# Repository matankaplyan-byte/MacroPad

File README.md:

# MacroPad

A fully customizable 6-key macro pad powered by a custom RP2040 PCB, featuring a rotary encoder, a 1.3-inch display, and a Python desktop application.

## The Idea

The goal is to create a macro pad with **unlimited custom layouts**.

Each layout contains six customizable macros. By pressing the rotary encoder's built-in button, users will be able to switch between layouts without opening the desktop application.

For example:

- **Layout 1 — Everyday:** WhatsApp, YouTube, Discord mute, media controls, etc.
- **Layout 2 — Programming:** Copy, paste, run code, open applications, and shortcuts.
- **Layout 3 — Sim Racing:** Game shortcuts and other racing-related controls.

Users will be able to create as many layouts as they want and customize the actions assigned to each key.

## Planned Hardware

- Custom RP2040-based PCB
- 6 mechanical keyboard switches
- EC11 rotary encoder with push button
- 1.3-inch ST7789 240×240 display
- USB-C connection
- Custom 3D-printed enclosure

The rotary encoder will control volume when rotated and switch between macro layouts when pressed.

The display is intended to show useful information about the currently selected layout and macros.

### PCB Design

I designed the custom PCB in KiCad, including the RP2040 microcontroller, USB-C connection, mechanical switches, rotary encoder, and display connector.

**Circuit schematic:**

**PCB layout:**

**PCB 3D preview:**

### 3D Modeling

I used Fusion 360 to design the enclosure and check how the components would fit together.

I imported models of the PCB components, including the switches, screen, and rotary encoder, to help position everything correctly.

**Component assembly in Fusion 360:**

The enclosure was designed as two separate pieces, with holes for heat-set inserts and screws to hold them together.

The first print still needs some improvements because the supports damaged the top part, but the bottom part printed successfully.

## Desktop Software

The controller is being developed in Python using Tkinter.

### Currently implemented

- Dark-themed desktop GUI
- Six selectable macro slots
- Arduino serial communication
- WhatsApp and YouTube launching
- Discord mute/unmute
- Media play/pause
- Custom macro editing
- Support for keyboard shortcuts, websites, and launching applications
- Creating and deleting custom layouts
- Saving layouts and macros using JSON
- Rotary encoder volume control in the Arduino prototype
- OLED display support in the Arduino prototype

### Planned features

- Expanding the physical button support from one to six buttons
- Adapting the Arduino Pro Micro code to the custom RP2040 PCB
- Updating the GPIO assignments
- Integrating the final ST7789 display
- Testing communication with the final hardware

## Current Prototype

An **Arduino Pro Micro with a single push button** is being used to test the software.

The Arduino sends button-press events to Python over USB Serial, allowing the desktop application to execute macros.

I also connected a 0.96-inch OLED display and rotary encoder to test the display functionality and volume controls.

**The Arduino Pro Micro is not part of the final hardware design.** It is only being used for development and testing while the custom PCB is being manufactured.

## Installation (Current Prototype)

Install the Python dependencies:

```bash
pip install -r requirements.txt
```

Connect the Arduino prototype, configure the correct COM port in `main.py`, and run:

```bash
python main.py
```

## Development Roadmap

- [x] Design custom RP2040 PCB
- [x] Create initial Python macro controller
- [x] Build Arduino button prototype
- [x] Create dark-themed GUI
- [x] Add custom macro editing
- [x] Implement JSON configuration saving
- [x] Implement unlimited custom layouts
- [x] Add rotary encoder controls
- [x] Finish the 3D-printed enclosure design
- [ ] Fix the enclosure print
- [ ] Manufacture and assemble the custom PCB
- [ ] Integrate the ST7789 display
- [ ] Test the final hardware

## Bill of Materials (BOM)

The complete Bill of Materials for the MacroPad, including component quantities, values, and LCSC part numbers, is available here:

[View the MacroPad BOM](macropad/macro_pad_BOM.csv)

## Hack Club Forge

This project is being developed for Hack Club Forge.

[View the project on Forge](https://forge.hackclub.com/projects/4199)

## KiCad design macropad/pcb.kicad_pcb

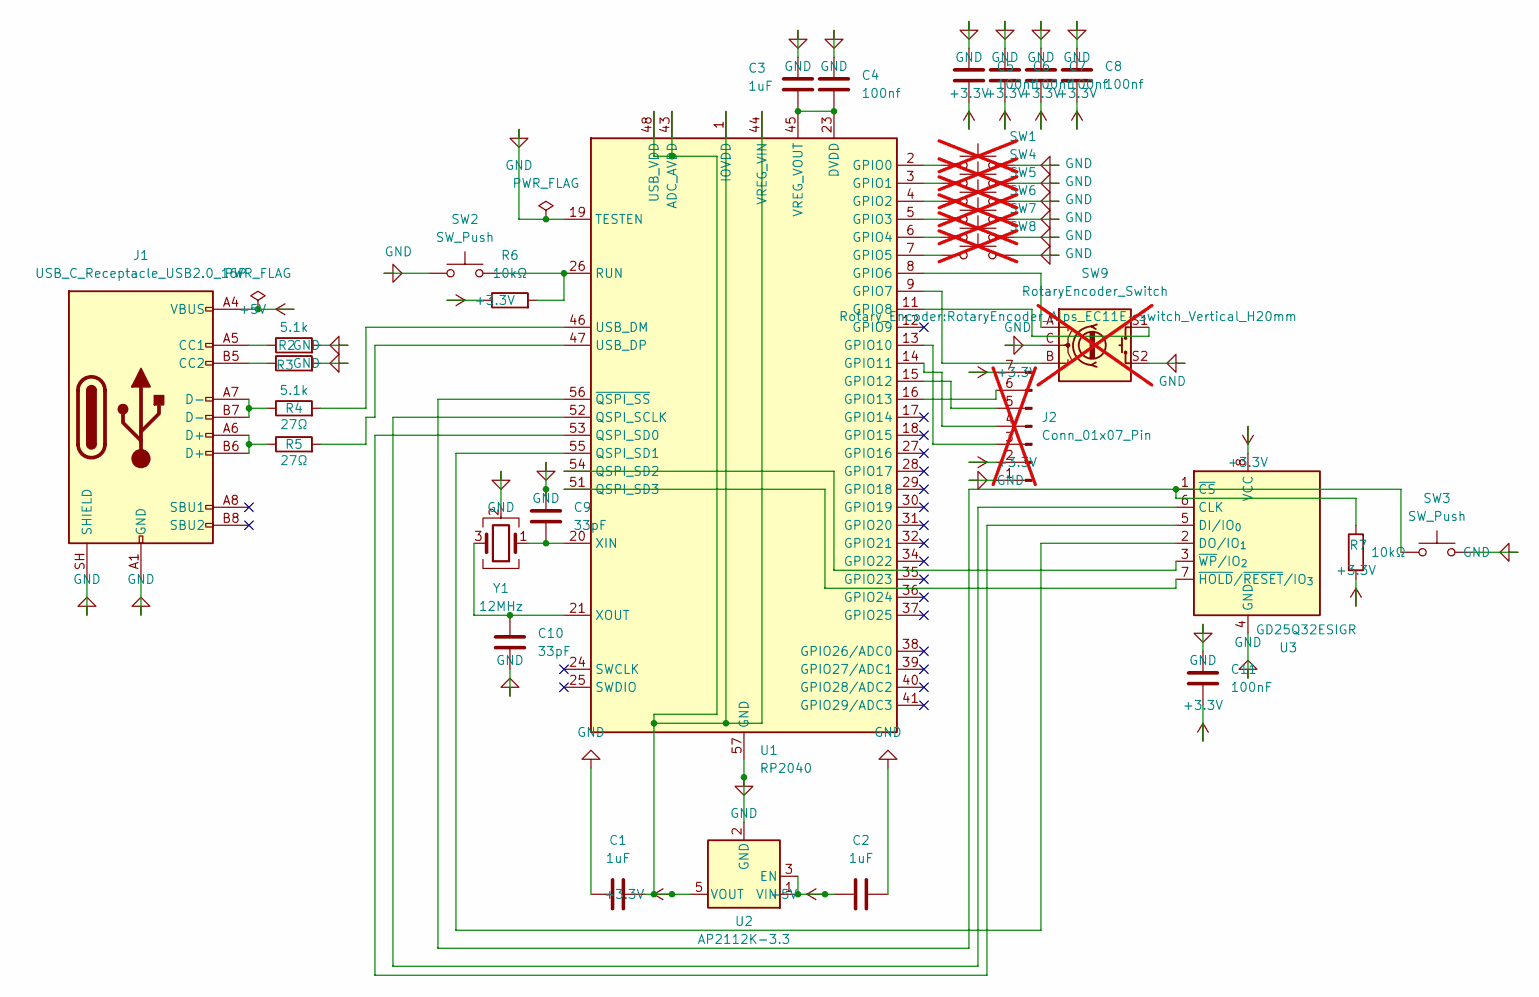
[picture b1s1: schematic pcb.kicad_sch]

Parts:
C1, C2, C3: 1uF; C_0603_1608Metric; LCSC C113807
C4, C5, C6, C7, C8: 100nf; C_0603_1608Metric; LCSC C49326065
C9, C10: 33pF; C_0603_1608Metric; LCSC C107047
C11: 100nF; C_0603_1608Metric; LCSC C49326065
J1: USB_C_Receptacle_USB2.0_16P; USB_C_Receptacle_HRO_TYPE-C-31-M-12; LCSC C165948
J2: Conn_01x07_Pin; PinHeader_1x07_P2.54mm_Vertical; not fitted
R2, R3: 5.1k; R_0603_1608Metric; LCSC C23186
R4, R5: 27Ω; R_0603_1608Metric; LCSC C25190
R6, R7: 10kΩ; R_0603_1608Metric; LCSC C25804
SW1, SW4, SW5, SW6, SW7, SW8: SW_Push; SW_Cherry_MX_1.00u_PCB; not fitted
SW2, SW3: SW_Push; SW_SPST_TL3342; LCSC C2886897
SW9: RotaryEncoder_Switch; RotaryEncoder_Alps_EC11E-Switch_Vertical_H20mm; not fitted
U1: RP2040; QFN-56-1EP_7x7mm_P0.4mm_EP3.2x3.2mm; LCSC C2040
U2: AP2112K-3.3; SOT-23-5; LCSC C51118
U3: GD25Q32ESIGR; SOIC-8_5.3x5.3mm_P1.27mm; LCSC C2832998
Y1: 12MHz; Crystal_SMD_3225-4Pin_3.2x2.5mm; LCSC C9002

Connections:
+3.3V: C1.2, C5.2, C6.2, C7.2, C8.2, C11.1, J2.2, J2.7, R6.1, R7.2, U1.1 (IOVDD), U1.10 (IOVDD), U1.22 (IOVDD), U1.33 (IOVDD), U1.42 (IOVDD), U1.43 (ADC_AVDD), U1.44 (VREG_VIN), U1.48 (USB_VDD), U1.49 (IOVDD), U2.5 (VOUT), U3.8 (VCC)
+5V: C2.1, J1.A4 (VBUS), J1.A9 (VBUS), J1.B4 (VBUS), J1.B9 (VBUS), U2.1 (VIN), U2.3 (EN)
GND: C1.1, C2.2, C3.1, C4.1, C5.1, C6.1, C7.1, C8.1, C9.1, C10.2, C11.2, J1.A1 (GND), J1.A12 (GND), J1.B1 (GND), J1.B12 (GND), J1.SH (SHIELD), J2.1, R2.2, R3.2, SW1.2, SW2.1, SW3.2, SW4.2, SW5.2, SW6.2, SW7.2, SW8.2, SW9.C, SW9.S2, U1.19 (TESTEN), U1.57 (GND), U2.2 (GND), U3.4 (GND), Y1.2 (G), Y1.4 (G)
unnamed: J1.A5 (CC1), R2.1
unnamed: J1.B5 (CC2), R3.1
unnamed: J1.A6 (D+), J1.B6 (D+), R5.1
unnamed: J1.A7 (D-), J1.B7 (D-), R4.1
unnamed: J2.3, U1.13 (GPIO10)
unnamed: J2.4, U1.14 (GPIO11)
unnamed: J2.5, U1.15 (GPIO12)
unnamed: J2.6, U1.16 (GPIO13)
unnamed: SW1.1, U1.2 (GPIO0)
unnamed: SW4.1, U1.3 (GPIO1)
unnamed: SW5.1, U1.4 (GPIO2)
unnamed: SW6.1, U1.5 (GPIO3)
unnamed: SW7.1, U1.6 (GPIO4)
unnamed: SW8.1, U1.7 (GPIO5)
unnamed: SW9.A, U1.8 (GPIO6)
unnamed: SW9.B, U1.9 (GPIO7)
unnamed: SW9.S1, U1.11 (GPIO8)
unnamed: U1.52 (QSPI_SCLK), U3.6 (CLK)
unnamed: U1.53 (QSPI_SD0), U3.5 (DI/IO_{0})
unnamed: U1.55 (QSPI_SD1), U3.2 (DO/IO_{1})
unnamed: U1.54 (QSPI_SD2), U3.3 (~WP/IO_{2})
unnamed: U1.51 (QSPI_SD3), U3.7 (~HOLD/~RESET/IO_{3})
unnamed: R6.2, SW2.2, U1.26 (RUN)
unnamed: R4.2, U1.46 (USB_DM)
unnamed: R5.2, U1.47 (USB_DP)
unnamed: C3.2, C4.2, U1.23 (DVDD), U1.45 (VREG_VOUT), U1.50 (DVDD)
unnamed: C9.2, U1.20 (XIN), Y1.1
unnamed: C10.1, U1.21 (XOUT), Y1.3
unnamed: R7.1, SW3.1, U1.56 (~QSPI_SS), U3.1 (~CS)

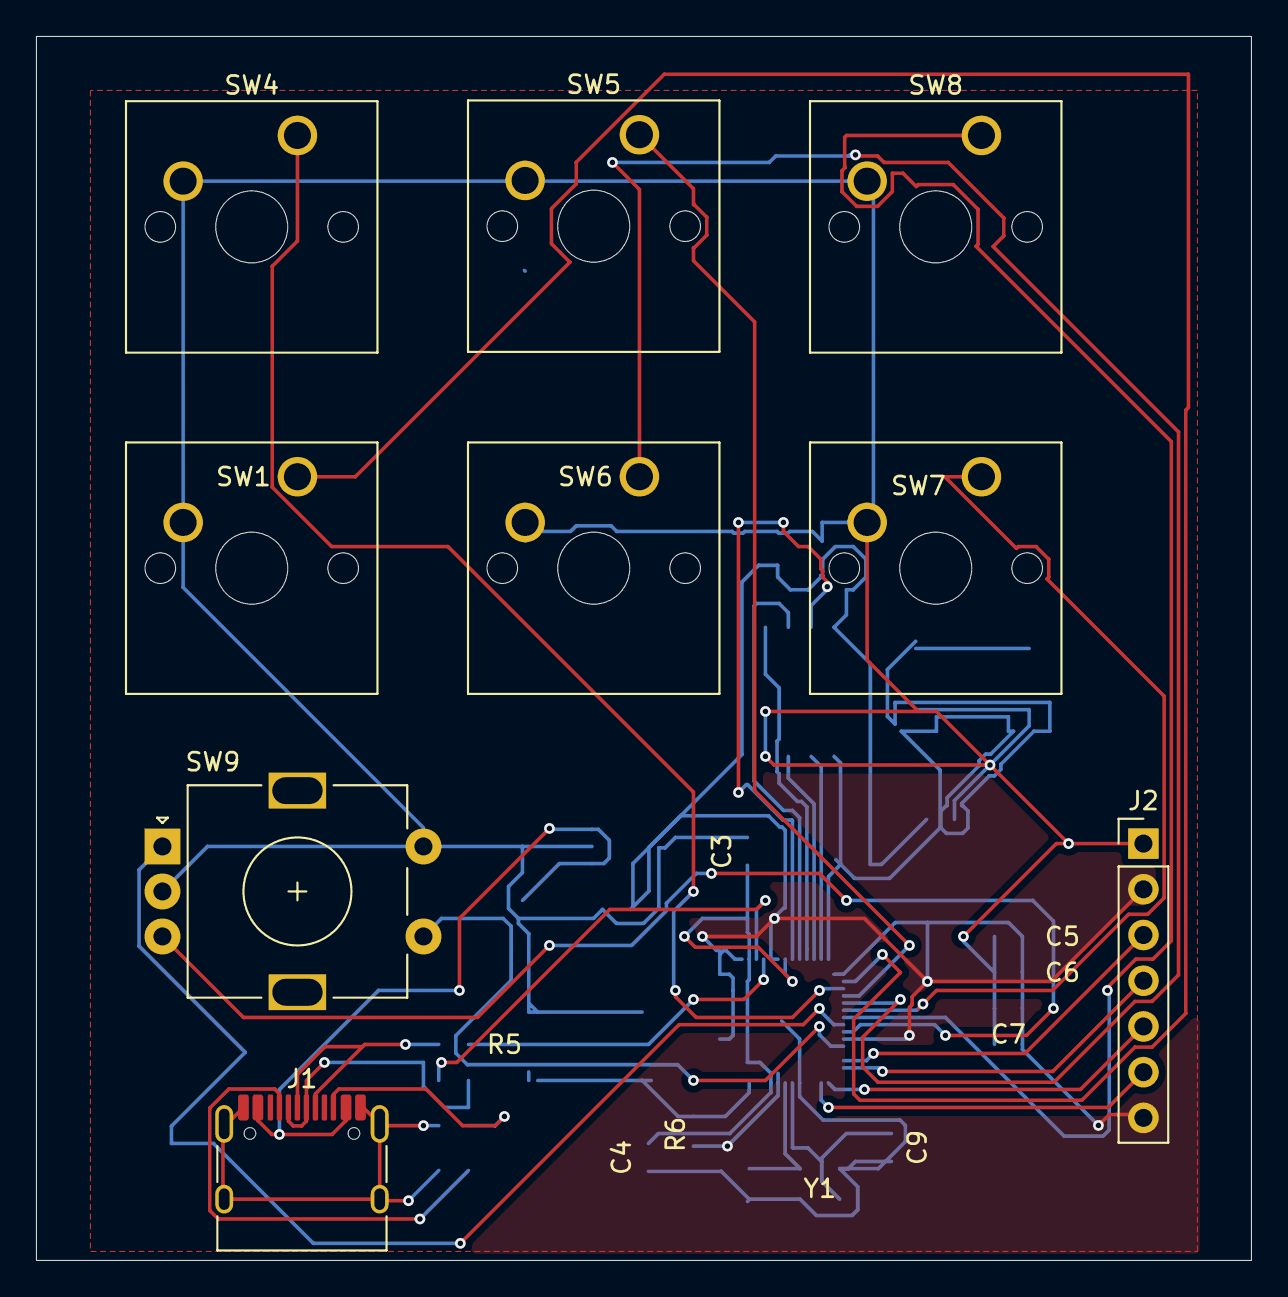
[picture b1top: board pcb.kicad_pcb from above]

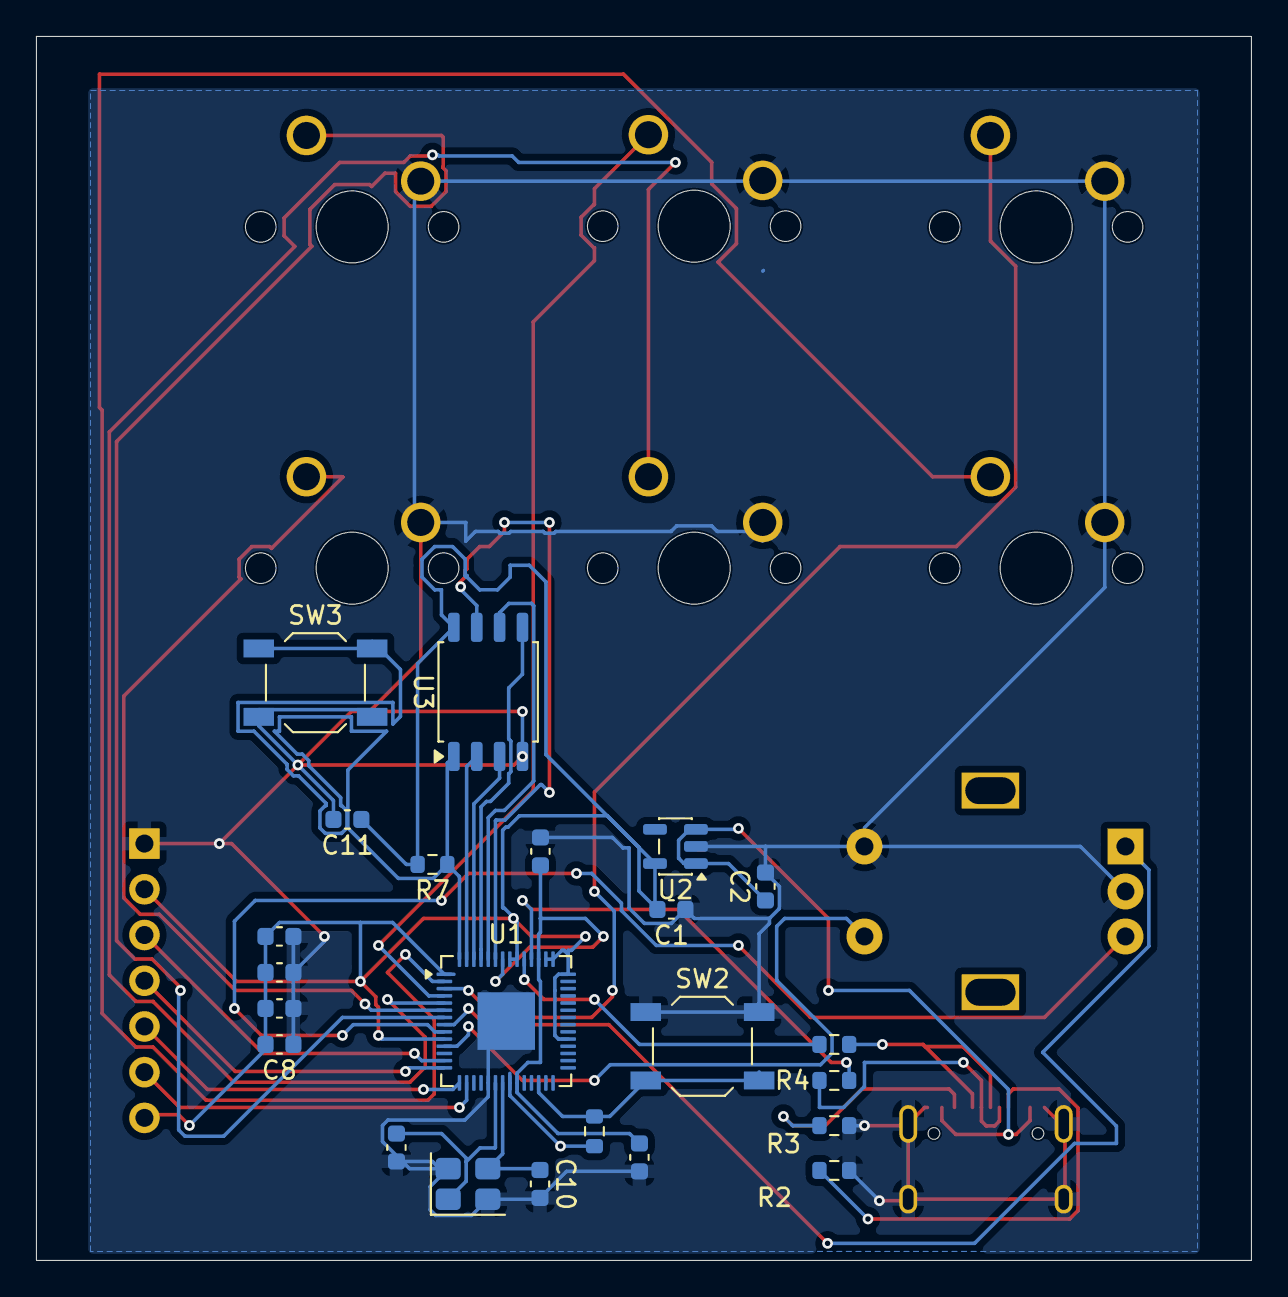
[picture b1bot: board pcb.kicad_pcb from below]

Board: 2 copper layers, 67.5 x 68.0 mm, 32 parts (23 on the bottom side), 32 nets.

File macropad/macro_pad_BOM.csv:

"Reference","Value","Footprint","Exclude from Board","Exclude from Simulation","Qty","LCSC"
"C1","1uF","Capacitor_SMD:C_0603_1608Metric","","","1","C113807"
"C2,C3","1uF","C_0603_1608Metric","","","2","C113807"
"C4,C5,C6,C7,C8","100nf","C_0603_1608Metric","","","5","C49326605"
"C9,C10","33pF","C_0603_1608Metric","","","2","C107047"
"C11","100nF","C_0603_1608Metric","","","1","C49326605"
"J1","USB_C_Receptacle_USB2.0_16P","Connector_USB:USB_C_Receptacle_HRO_TYPE-C-31-M-12","","","1","C165948"
"J2","Conn_01x07_Pin","Connector_PinHeader_2.54mm:PinHeader_1x07_P2.54mm_Vertical","Excluded from board","","1",""
"R2,R3","5.1k","Resistor_SMD:R_0603_1608Metric","","","2","C23186"
"R4,R5","27Ω","Resistor_SMD:R_0603_1608Metric","","","2","C25190"
"R6,R7","10kΩ","Resistor_SMD:R_0603_1608Metric","","","2","C25804"
"SW1,SW4,SW5,SW6,SW7,SW8","SW_Push","Button_Switch_Keyboard:SW_Cherry_MX_1.00u_PCB","Excluded from board","","6",""
"SW2,SW3","SW_Push","SW_SPST_TL3342","","","2","C2886897"
"SW9","RotaryEncoder_Switch","Rotary_Encoder:RotaryEncoder_Alps_EC11E-Switch_Vertical_H20mm","","","1",""
"U1","RP2040","Package_DFN_QFN:QFN-56-1EP_7x7mm_P0.4mm_EP3.2x3.2mm","","","1","C2040"
"U2","AP2112K-3.3","Package_TO_SOT_SMD:SOT-23-5","","","1","C51118"
"U3","GD25Q32ESIGR","Package_SO:SOIC-8_5.3x5.3mm_P1.27mm","","","1","C2832998"
"Y1","12MHz","Crystal:Crystal_SMD_3225-4Pin_3.2x2.5mm","","","1","C9002"
